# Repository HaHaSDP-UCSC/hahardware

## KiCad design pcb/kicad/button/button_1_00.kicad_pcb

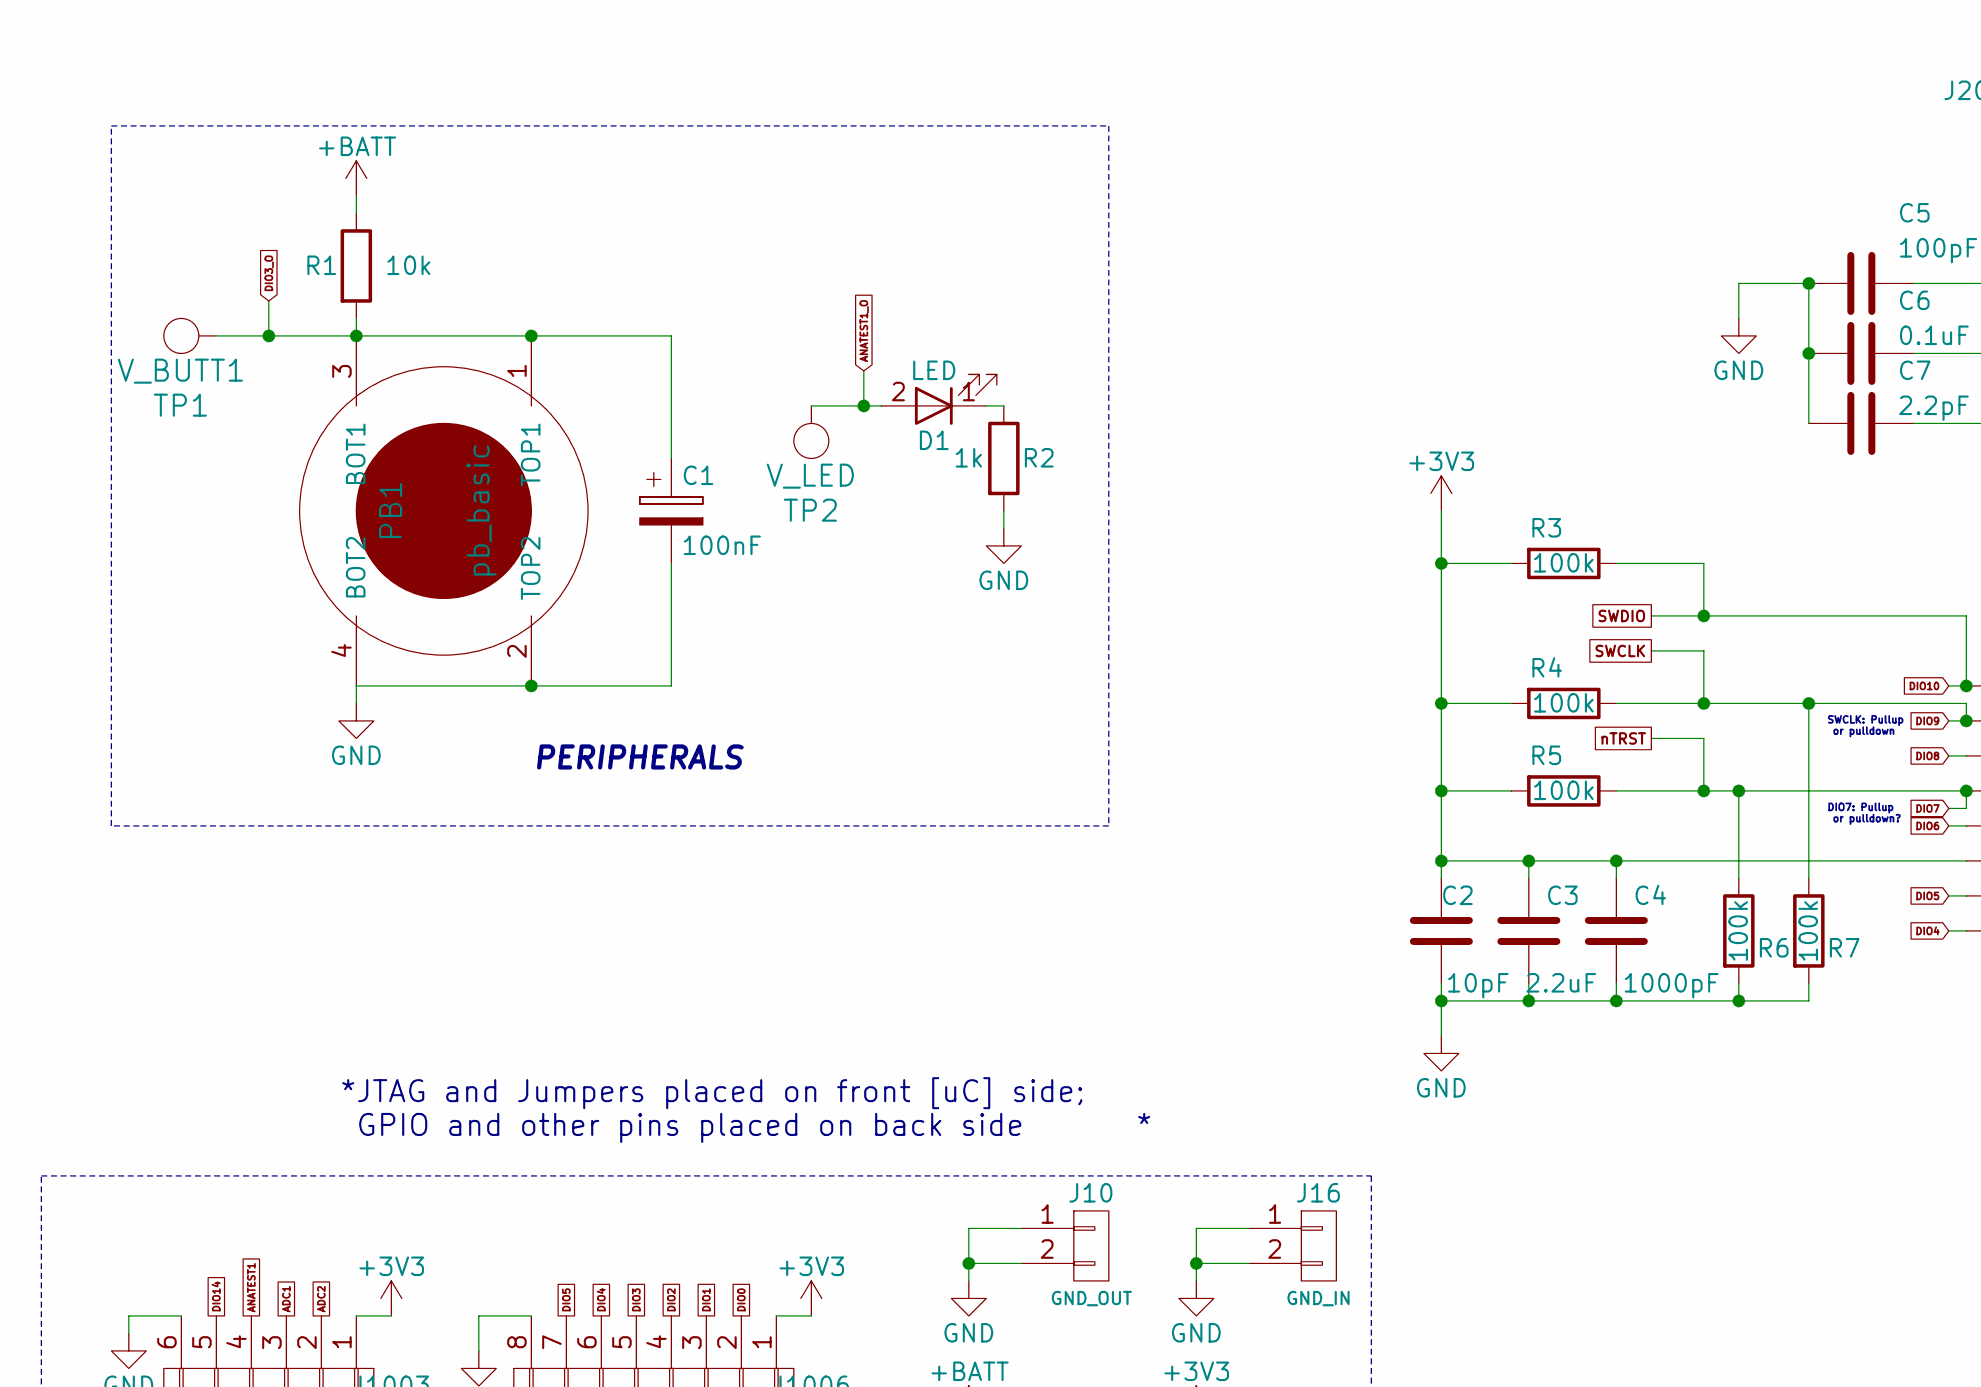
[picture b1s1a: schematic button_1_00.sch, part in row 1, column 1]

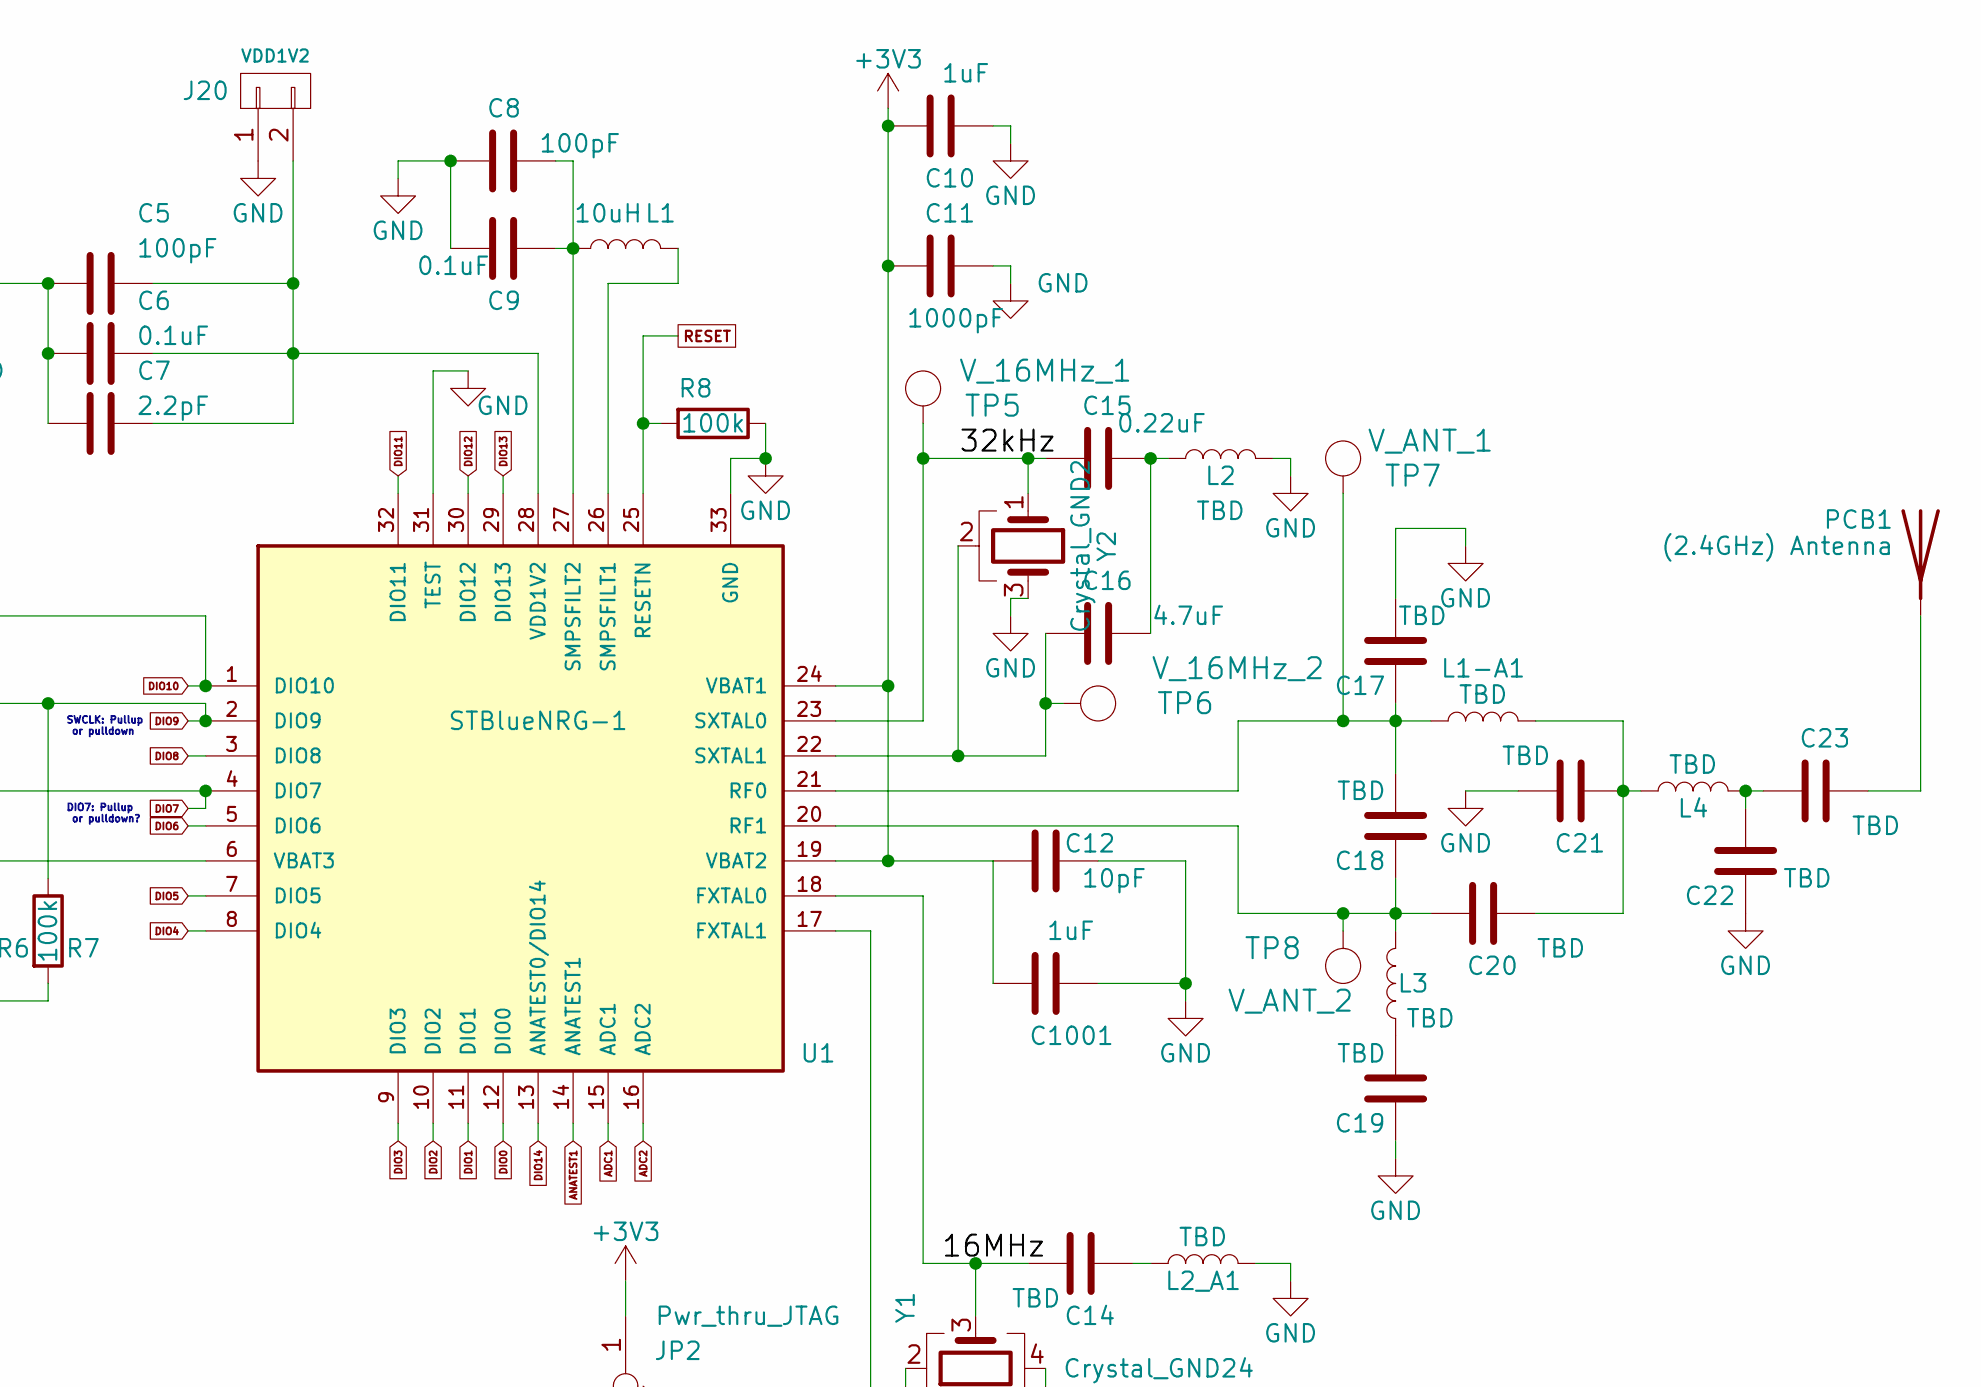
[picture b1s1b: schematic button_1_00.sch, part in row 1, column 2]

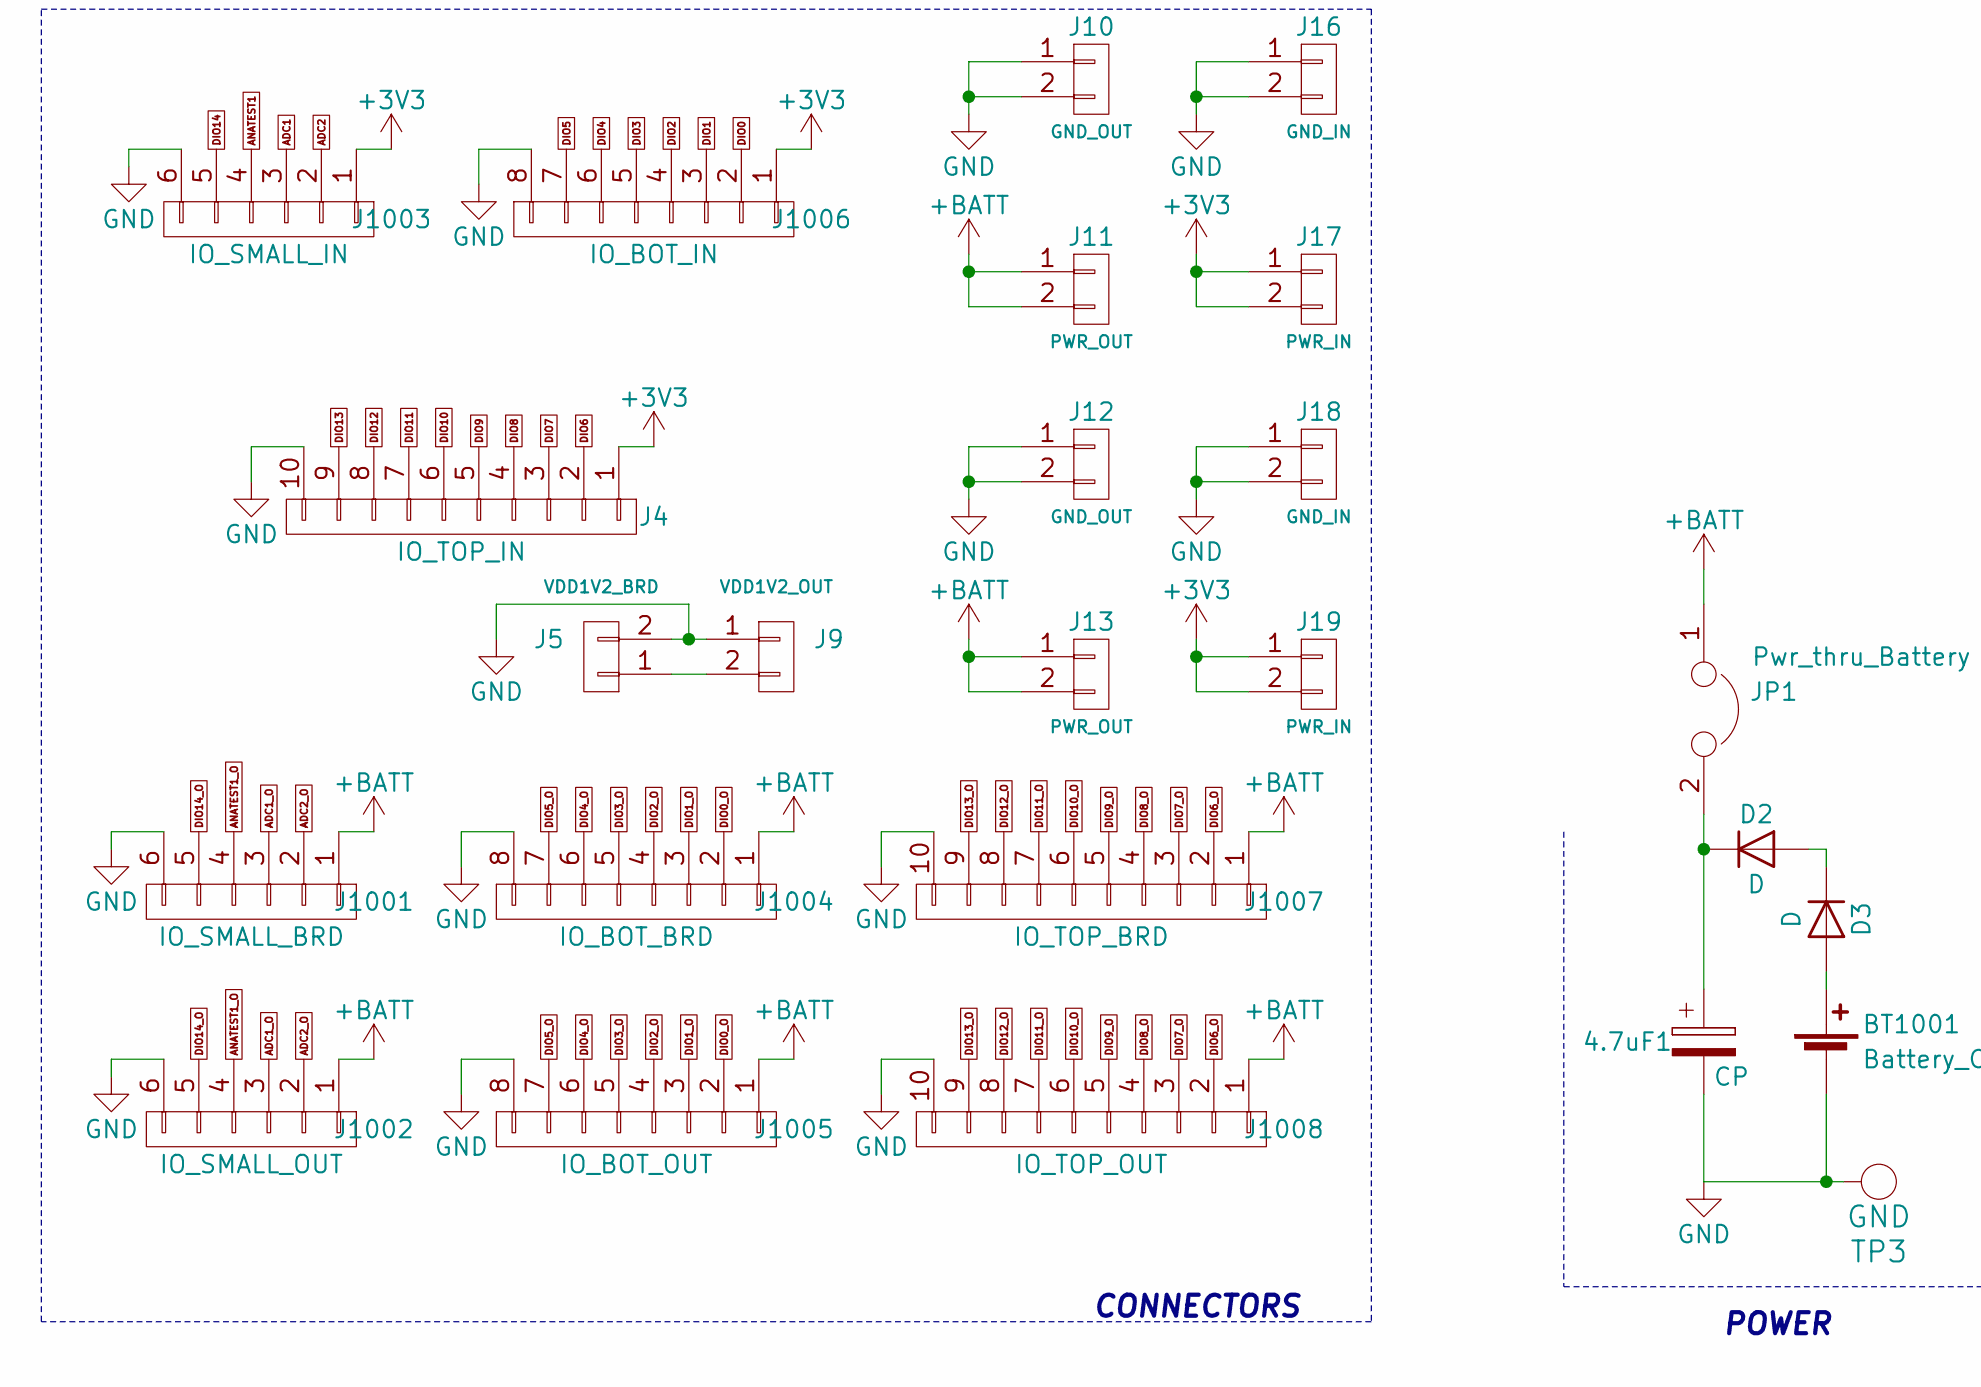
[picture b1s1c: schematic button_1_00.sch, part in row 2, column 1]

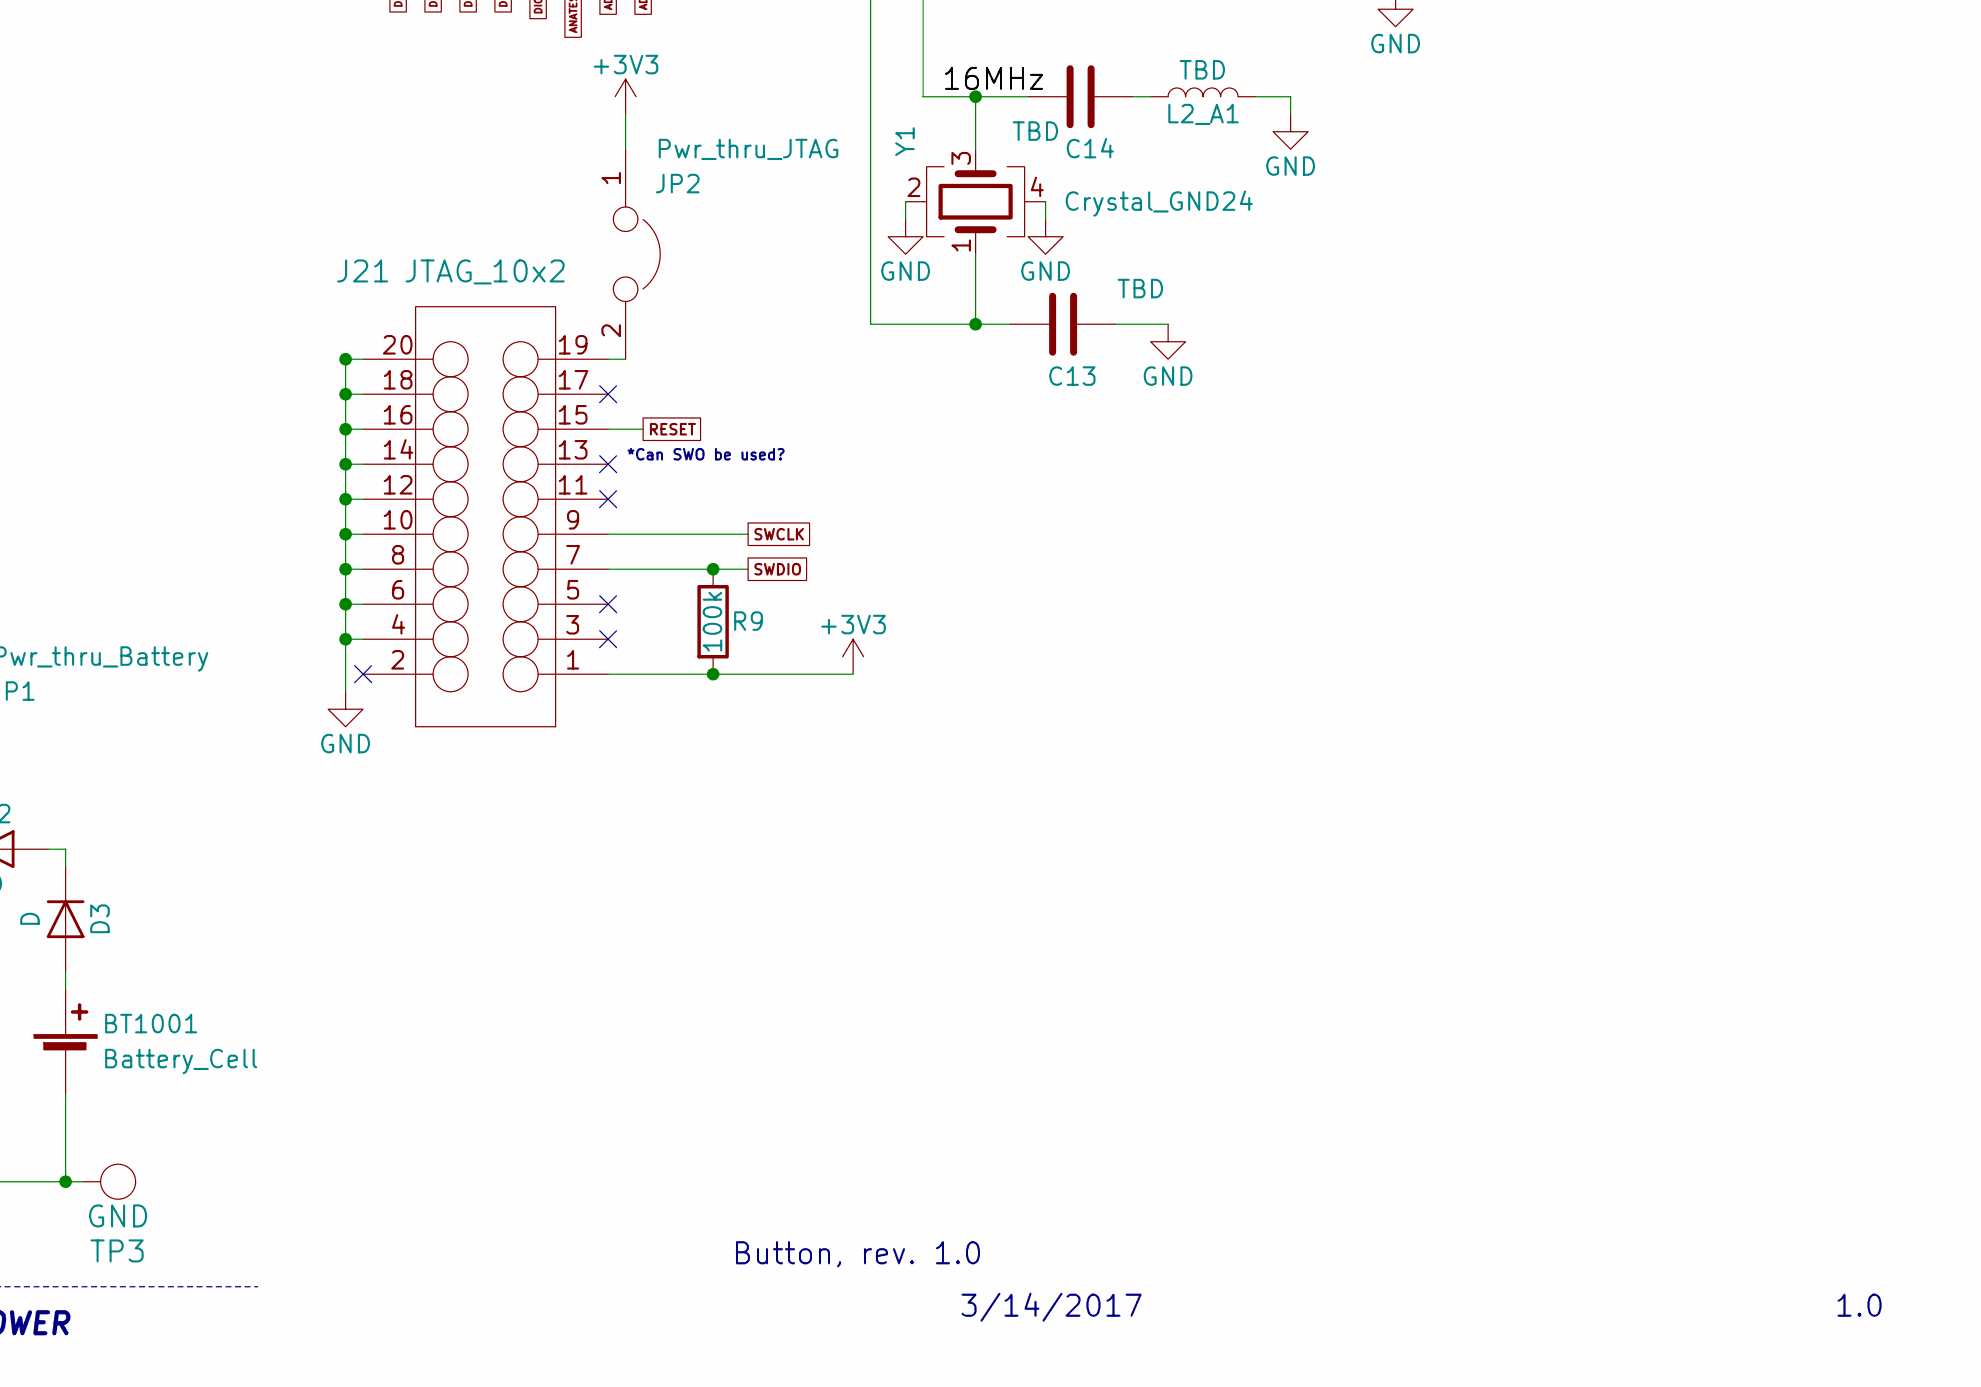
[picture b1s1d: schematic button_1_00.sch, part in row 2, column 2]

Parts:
4.7uF1: CP; C_0603
BT1001: Battery_Cell; Pin_Header_Straight_1x02_Pitch2.54mm
C1: 100nF; C_0603_HandSoldering
C2, C12: 10pF; C_0402
C3: 2.2uF; C_0402
C4, C11: 1000pF; C_0402
C5, C8: 100pF; C_0402
C6, C9: 0.1uF; C_0603
C7: 2.2pF; C_0402
C10, C1001: 1uF; C_0603
C13, C14, C17, C18, C19, C20, C21, C22, C23: TBD; C_0402
C15: 0.22uF; C_0402
C16: 4.7uF; C_0402
D1: LED; LED_0603
D2, D3: D; D_0603
J4: IO_TOP_IN; Pin_Header_Straight_1x10_Pitch2.54mm
J5: VDD1V2_BRD; Pin_Header_Straight_1x02_Pitch2.54mm
J9: VDD1V2_OUT; Pin_Header_Straight_1x02_Pitch2.54mm
J10, J12: GND_OUT; Pin_Header_Straight_1x02_Pitch2.54mm
J11, J13: PWR_OUT; Pin_Header_Straight_1x02_Pitch2.54mm
J16, J18: GND_IN; Pin_Header_Straight_1x02_Pitch2.54mm
J17, J19: PWR_IN; Pin_Header_Straight_1x02_Pitch2.54mm
J20: VDD1V2; Pin_Header_Straight_1x02_Pitch2.54mm
J21: JTAG_10x2; Multicomp_MC9A12-2034_2x10x2.54mm_Straight
J1001: IO_SMALL_BRD; Pin_Header_Straight_1x06_Pitch2.54mm
J1002: IO_SMALL_OUT; Pin_Header_Straight_1x06_Pitch2.54mm
J1003: IO_SMALL_IN; Pin_Header_Straight_1x06_Pitch2.54mm
J1004: IO_BOT_BRD; Pin_Header_Straight_1x08_Pitch2.54mm
J1005: IO_BOT_OUT; Pin_Header_Straight_1x08_Pitch2.54mm
J1006: IO_BOT_IN; Pin_Header_Straight_1x08_Pitch2.54mm
J1007: IO_TOP_BRD; Pin_Header_Straight_1x10_Pitch2.54mm
J1008: IO_TOP_OUT; Pin_Header_Straight_1x10_Pitch2.54mm
JP1: Pwr_thru_Battery; Pin_Header_Straight_1x02_Pitch2.54mm
JP2: Pwr_thru_JTAG; Pin_Header_Straight_1x02_Pitch2.54mm
L1: 10uH; Neosid_Inductor_SM-NE29_SMD1008
L1-A1, L2, L2_A1, L3, L4: TBD; Neosid_Inductor_SM0603CG
PB1: pb_basic
PCB1: (2.4GHz) Antenna; Molex_SMA_Jack_Edge_Mount
R1: 10k; R_0603
R2: 1k; R_0603
R3, R4, R5, R6, R7, R8: 100k; R_0603
R9: 100k; R_0805
TP1: V_BUTT1; TP_gen
TP2: V_LED; TP_gen
TP3: GND; TP_gen
TP5: V_16MHz_1; TP_gen
TP6: V_16MHz_2; TP_gen
TP7: V_ANT_1; TP_gen
TP8: V_ANT_2; TP_gen
U1: STBlueNRG-1; STBNRG1
Y1: Crystal_GND24; Crystal_SMD_2520-4pin_2.5x2.0mm
Y2: Crystal_GND2; Crystal_C26-LF_d2.1mm_l6.5mm_Horizontal_1EP_style1

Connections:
+3V3: C2.2, C3.2, C4.2, C10.2, C11.2, C12.2, C1001.2, J4.1, J17.1, J17.2, J19.1, J19.2, J21.1 (U_TG), J1003.1, J1006.1, JP2.1, R3.2, R4.2, R5.2, R9.2, U1.6 (VBAT3), U1.19 (VBAT2), U1.24 (VBAT1)
+BATT: J11.1, J11.2, J13.1, J13.2, J1001.1, J1002.1, J1004.1, J1005.1, J1007.1, J1008.1, JP1.1, R1.1
/16MHz: C14.2, U1.18 (FXTAL0), Y1.3
/32kHz: C15.2, TP5.1, U1.23 (SXTAL0), Y2.1
ADC1: J1003.3, U1.15 (ADC1)
ADC1_O: J1001.3, J1002.3
ADC2: J1003.2, U1.16 (ADC2)
ADC2_O: J1001.2, J1002.2
ANATEST1: J1003.4, U1.14 (ANATEST1)
ANATEST1_O: D1.2 (A), J1001.4, J1002.4, TP2.1
DIO0: J1006.2, U1.12 (DIO0)
DIO0_O: J1004.2, J1005.2
DIO1: J1006.3, U1.11 (DIO1)
DIO1_O: J1004.3, J1005.3
DIO2: J1006.4, U1.10 (DIO2)
DIO2_O: J1004.4, J1005.4
DIO3: J1006.5, U1.9 (DIO3)
DIO3_O: C1.1, J1004.5, J1005.5, PB1.1 (TOP1), PB1.3 (BOT1), R1.2, TP1.1
DIO4: J1006.6, U1.8 (DIO4)
DIO4_O: J1004.6, J1005.6
DIO5: J1006.7, U1.7 (DIO5)
DIO5_O: J1004.7, J1005.7
DIO6: J4.2, U1.5 (DIO6)
DIO6_O: J1007.2, J1008.2
DIO7: J4.3, R5.1, R6.1, U1.4 (DIO7)
DIO7_O: J1007.3, J1008.3
DIO8: J4.4, U1.3 (DIO8)
DIO8_O: J1007.4, J1008.4
DIO9: J4.5, J21.9 (TCK/SWCLK), R4.1, R7.1, U1.2 (DIO9)
DIO9_O: J1007.5, J1008.5
DIO10: J4.6, J21.7 (TMS/SWDIO), R3.1, R9.1, U1.1 (DIO10)
DIO10_O: J1007.6, J1008.6
DIO11: J4.7, U1.32 (DIO11)
DIO11_O: J1007.7, J1008.7
DIO12: J4.8, U1.30 (DIO12)
DIO12_O: J1007.8, J1008.8
DIO13: J4.9, U1.29 (DIO13)
DIO13_O: J1007.9, J1008.9
DIO14: J1003.5, U1.13 (ANATEST0/DIO14)
DIO14_O: J1001.5, J1002.5
GND: 4.7uF1.2, BT1001.2 (-), C1.2, C2.1, C3.1, C4.1, C5.2, C6.2, C7.2, C8.2, C9.2, C10.1, C11.1, C12.1, C13.1, C17.2, C19.1, C21.2, C22.1, C1001.1, J4.10, J5.2, J9.1, J10.1, J10.2, J12.1, J12.2, J16.1, J16.2, J18.1, J18.2, J20.1, J21.4 (GND), J21.6 (GND), J21.8 (GND), J21.10 (GND), J21.12 (GND), J21.14 (GND), J21.16 (GND), J21.18 (GND), J21.20 (GND), J1001.6, J1002.6, J1003.6, J1004.8, J1005.8, J1006.8, J1007.10, J1008.10, L2.2, L2_A1.2, PB1.2 (TOP2), PB1.4 (BOT2), R2.2, R6.2, R7.2, R8.1, TP3.1, U1.31 (TEST), U1.33 (GND), Y1.2, Y1.4, Y2.3
unnamed: 4.7uF1.1, D2.1 (K), JP1.2
unnamed: BT1001.1 (+), D3.2 (A)
unnamed: C5.1, C6.1, C7.1, J20.2, U1.28 (VDD1V2)
unnamed: C8.1, C9.1, L1.1, U1.27 (SMPSFILT2)
unnamed: C13.2, U1.17 (FXTAL1), Y1.1
unnamed: C14.1, L2_A1.1
unnamed: C15.1, C16.1, L2.1
unnamed: C16.2, TP6.1, U1.22 (SXTAL1), Y2.2
unnamed: C17.1, C18.2, L1-A1.1, TP7.1, U1.21 (RF0)
unnamed: C18.1, C20.2, L3.2, TP8.1, U1.20 (RF1)
unnamed: C19.2, L3.1
unnamed: C20.1, C21.1, L1-A1.2, L4.1
unnamed: C22.2, C23.2, L4.2
unnamed: C23.1, PCB1.1
unnamed: D1.1 (K), R2.1
unnamed: D2.2 (A), D3.1 (K)
unnamed: J5.1, J9.2
unnamed: J21.19 (U_TGPWR), JP2.2
unnamed: L1.2, U1.26 (SMPSFILT1)
RESET: J21.15 (nSRST), R8.2, U1.25 (RESETN)

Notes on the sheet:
Button, rev. 1.0
1.0
3/14/2017
POWER
CONNECTORS
PERIPHERALS
*JTAG and Jumpers placed on front [uC] side; GPIO and other pins placed on back side *
DIO7: Pullup or pulldown?
SWCLK: Pullup or pulldown
*Can SWO be used?

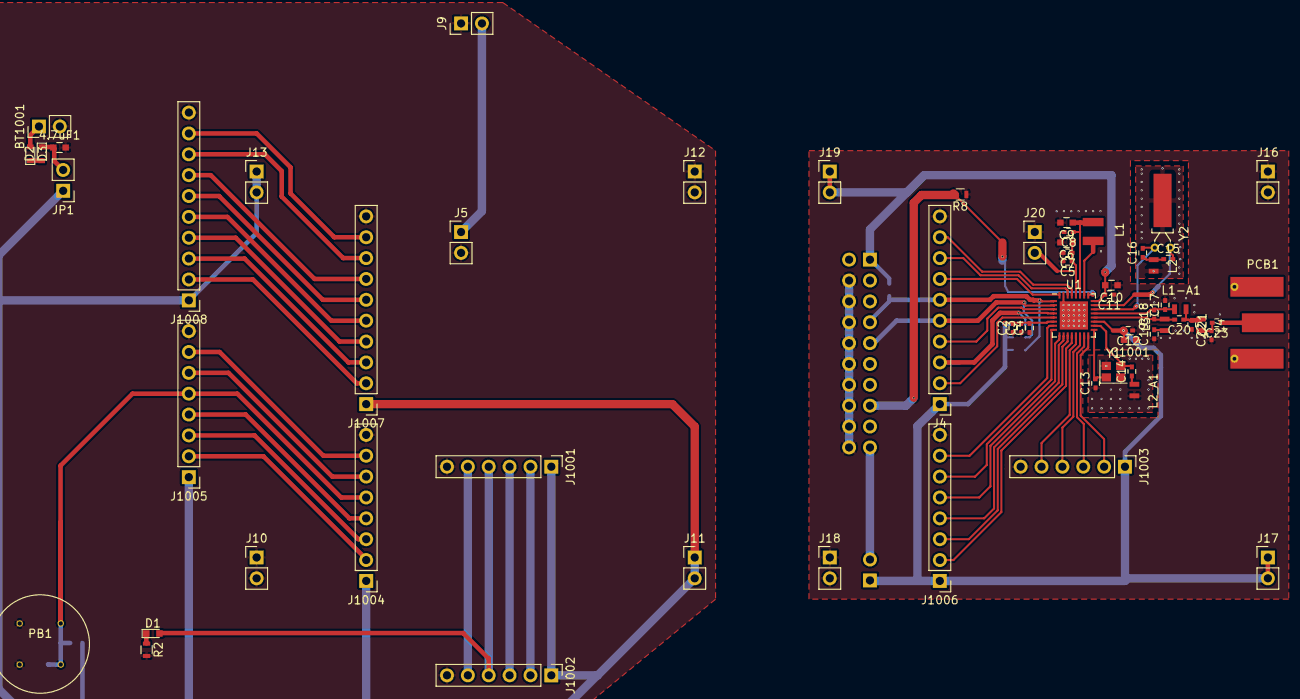
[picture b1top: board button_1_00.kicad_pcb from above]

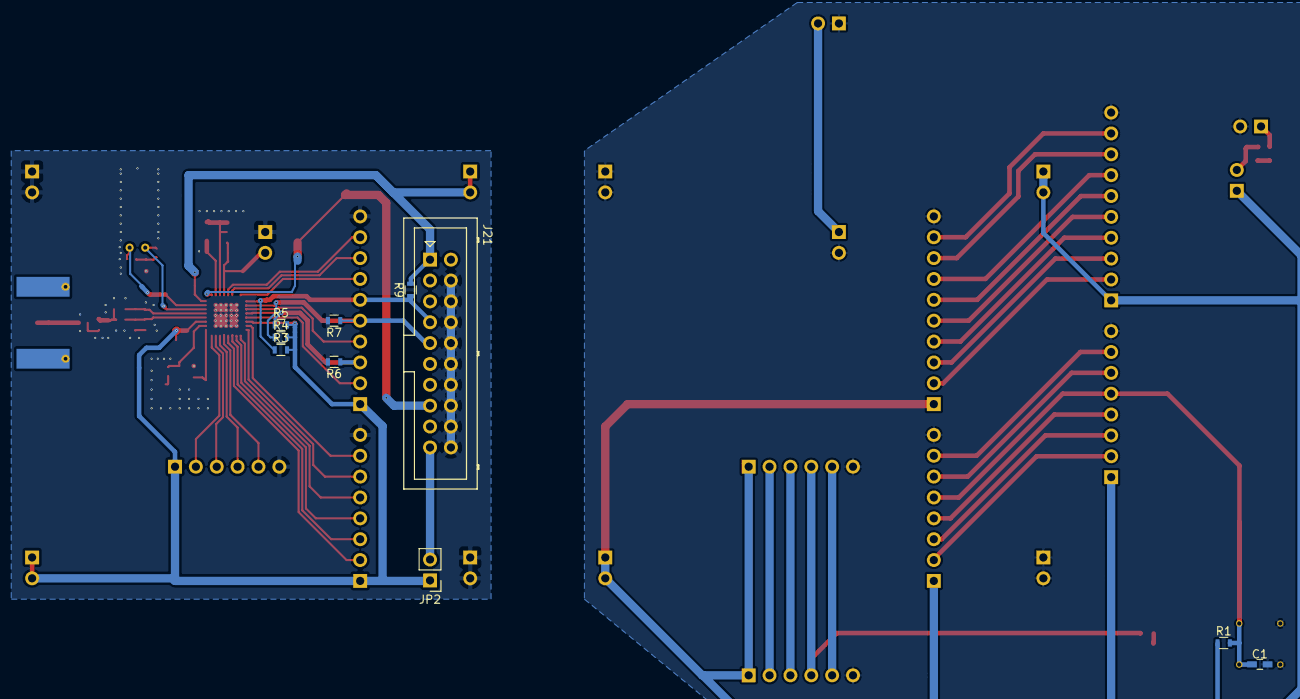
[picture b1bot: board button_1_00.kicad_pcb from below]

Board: 2 copper layers, 72 parts (10 on the bottom side), 61 nets.

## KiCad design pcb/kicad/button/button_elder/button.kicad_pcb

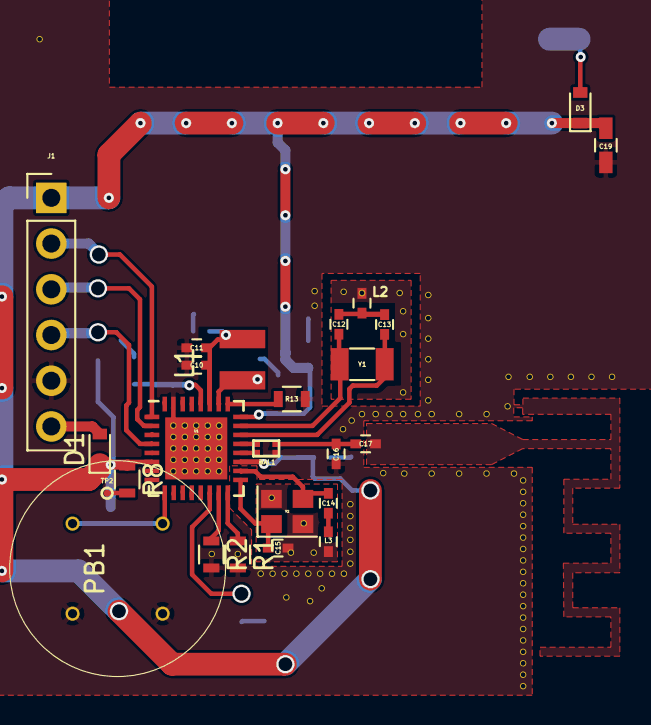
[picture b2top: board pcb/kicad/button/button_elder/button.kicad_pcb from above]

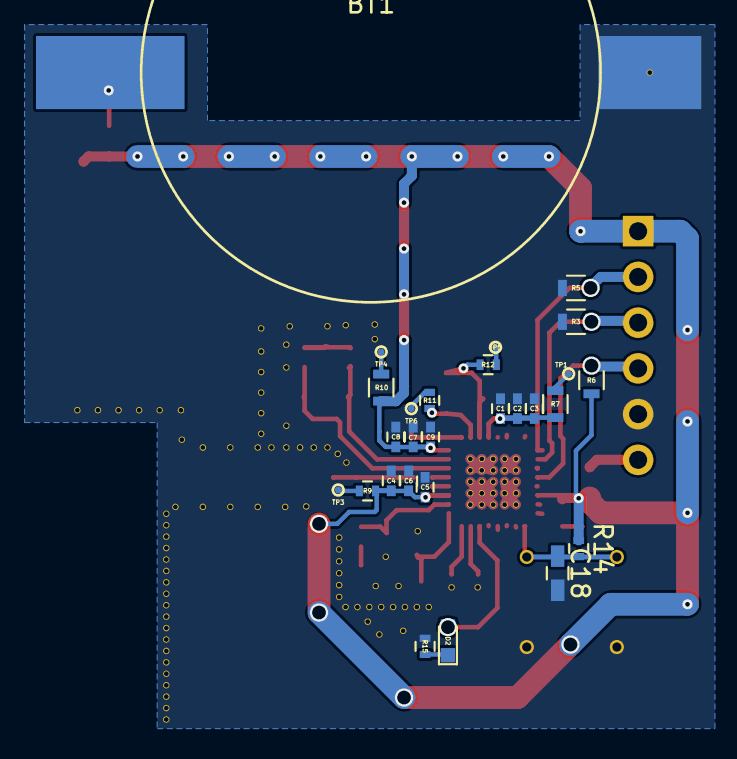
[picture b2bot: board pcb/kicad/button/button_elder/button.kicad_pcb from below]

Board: 2 copper layers, 52 parts (27 on the bottom side), 31 nets.

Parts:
BAL1: STBNR1_balun; BNRG1_balun
BT1: Battery_Cell; SMD_CoinCell
C1, C11: 100pF; C_0402
C2, C10: 0.1uF; C_0402
C3: 2.2pF; C_0402
C4, C9: 1000pF; C_0402
C5: 2.2uF; C_0402
C6, C7: 10pF; C_0402
C8: 1uF; C_0402
C12: 27pF; C_0402
C13, C14: 22pF; C_0402
C15: 18pF; C_0402
C16, C17: TBD; C_0402
C18: CP; C_0603_HandSoldering
C19: 1uF; C_0603_HandSoldering
D1: Power thru SWD; D_0603
D2: LED; LED_0603
D3: Power thru Battery; D_0603
J1: SWD with less; Pin_Header_Straight_1x06_Pitch2.54mm
L1: 10uH; Neosid_Inductor_SM-NE29_SMD1008
L2, L3: RFC; L_0402
PB1: pb_basic
R1, R2, R3, R5, R6, R13: 100k; R_0603
R7, R8, R10: 1k; R_0603
R9, R11, R12, R15: 1k; R_0402
R14: 10k; R_0402
TP1: VDD1V2; Measurement_Point_Round-SMD-tiniest
TP2, TP4: VBATT3; Measurement_Point_Round-SMD-tiniest
TP3: VBATT2; Measurement_Point_Round-SMD-tiniest
TP5: SMSPFILT2; Measurement_Point_Round-SMD-tiniest
TP6: SMPSFILT1; Measurement_Point_Round-SMD-tiniest
U1: STBlueNRG-1; STBNRG1
Y1: Xtal 32.768kHz; Crystal_SMD_3215-2pin_3.2x1.5mm
Y2: XTAL 16MHz; Crystal_SMD_2520-4pin_2.5x2.0mm

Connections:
+3V3: C4.2, C5.2, C6.2, C7.2, C8.2, C9.2, C19.1, D1.1, D3.1, J1.1, R6.2, R8.1, R9.1, R10.1, R14.1, U1.6, U1.19, U1.24
ADC1: R2.1, U1.15
ADC2: R1.1, U1.16
ANATEST1: D2.2, U1.14
DIO3: C18.1, PB1.1, PB1.3, R14.2, U1.9
DIO7: J1.4, R6.1, U1.4
DIO9: J1.3, R3.1, U1.2
DIO10: J1.2, R5.2, U1.1
GND: BAL1.4, BT1.2, C1.2, C2.2, C3.2, C4.1, C5.1, C6.1, C7.1, C8.1, C9.1, C10.2, C11.1, C15.1, C16.2, C17.1, C18.2, C19.2, J1.5, L2.2, L3.2, PB1.2, PB1.4, R1.2, R2.2, R3.2, R5.1, R13.2, R15.2, U1.31, U1.33, Y2.2, Y2.4
unnamed: BAL1.3, C16.1, C17.2
unnamed: BT1.1, D3.2
unnamed: C1.1, C2.1, C3.1, R7.1, U1.28
unnamed: C10.1, C11.2, L1.2, R12.2, U1.27
unnamed: C12.1, C13.1, L2.1
unnamed: C12.2, U1.23, Y1.1
unnamed: C13.2, U1.22, Y1.2
unnamed: C14.1, L3.1
unnamed: C14.2, U1.18, Y2.3
unnamed: C15.2, U1.17, Y2.1
unnamed: D1.2, J1.6
unnamed: D2.1, R15.1
unnamed: L1.1, R11.1, U1.26
unnamed: R7.2, TP1.1
unnamed: R8.2, TP2.1
unnamed: R9.2, TP3.1
unnamed: R10.2, TP4.1
unnamed: R11.2, TP6.1
unnamed: R12.1, TP5.1
RESET: R13.1, U1.25
RF0: BAL1.1, U1.21
RF1: BAL1.2, U1.20

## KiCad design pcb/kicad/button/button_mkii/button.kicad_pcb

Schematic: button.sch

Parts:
C1, C22: 1uF; C_0805
C2, C23: 0.1uF; C_0603
C3, C24: 0.01uF; C_0402
C4, C7: 0.01uF; C_0805
C5, C8: 1000pF; C_0603
C6, C9: 10pF; C_0402
C10: 0.1uF; C_0402
C11: 100pF; C_0402
C12, C14: 27pF; C_0402
C13: 22pF; C_0402
C15: 33pF; C_0402
C20, C21: 1uF; C_0402
J1: SWD; Pin_Header_Straight_1x08_Pitch2.54mm
J2: RESET_CONN; Pin_Header_Straight_1x02_Pitch2.54mm
J3: ADC_OUT; Pin_Header_Straight_1x03_Pitch2.54mm
L1: 10uH; Neosid_Inductor_SM-NE29_SMD1008
R3, R4, R5, R13: 100k; R_0402
R6, R9, R11, R12, R16: 1k; R_0402
R7, R8, R10: 1k; R_0603
TP1: VDD1V2; Measurement_Point_Round-SMD-tiniest
TP2, TP4: VBATT3; Measurement_Point_Round-SMD-tiniest
TP3: VBATT2; Measurement_Point_Round-SMD-tiniest
TP5: SMSPFILT2; Measurement_Point_Round-SMD-tiniest
TP6: SMPSFILT1; Measurement_Point_Round-SMD-tiniest
TP7: Xtal32MHz; Measurement_Point_Round-SMD-tiniest
TP8: Xtal32kHz; Measurement_Point_Round-SMD-tiniest
U1: STBlueNRG-1; STBNRG1
U2: TLV1117LV-3V; SOT-223
Y1: Xtal 32.768kHz; Crystal_SMD_3215-2pin_3.2x1.5mm
Y2: XTAL 32MHz; Crystal_SMD_2520-4pin_2.5x2.0mm

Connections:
/DIO2_LED: U1.10 (DIO2); also elsewhere on the board
/DIO12_BUTTON: U1.30 (DIO12); also elsewhere on the board
/RF0: U1.21 (RF0); also elsewhere on the board
/RF1: U1.20 (RF1); also elsewhere on the board
ADC1: J3.2, U1.15 (ADC1)
ADC2: J3.3, U1.16 (ADC2)
DIO7: J1.4, R4.2, U1.4 (DIO7)
DIO9: J1.5, R3.1, U1.2 (DIO9)
DIO10: J1.6, R5.2, U1.1 (DIO10)
GND: C1.2, C2.2, C3.2, C4.2, C5.2, C6.2, C7.1, C8.1, C9.1, C10.2, C11.1, C12.1, C13.1, C14.1, C15.1, C20.1, C21.1, C22.1, C23.1, C24.1, J1.7, J2.2, J3.1, R3.2, R5.1, R13.1, U1.31 (TEST), U1.33 (GND), U2.1 (GND), Y2.2, Y2.4; also elsewhere on the board
unnamed: C1.1, C2.1, C3.1, R7.2, U1.28 (VDD1V2)
unnamed: C10.1, C11.2, L1.2, R12.2, U1.27 (SMPSFILT2)
unnamed: C12.2, R16.1, U1.23 (SXTAL0), Y1.1
unnamed: C13.2, U1.22 (SXTAL1), Y1.2
unnamed: C14.2, R6.1, U1.18 (FXTAL0), Y2.3
unnamed: C15.2, U1.17 (FXTAL1), Y2.1
unnamed: C20.2, J1.1, U2.3 (VIN)
unnamed: J1.2, U1.12 (DIO0)
unnamed: J1.3, U1.11 (DIO1)
unnamed: J2.1, R13.2, U1.25 (RESETN)
unnamed: L1.1, R11.1, U1.26 (SMPSFILT1)
unnamed: R6.2, TP7.1
unnamed: R7.1, TP1.1
unnamed: R8.1, TP2.1
unnamed: R9.2, TP3.1
unnamed: R10.2, TP4.1
unnamed: R11.2, TP6.1
unnamed: R12.1, TP5.1
unnamed: R16.2, TP8.1

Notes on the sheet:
Button, rev 2.0
1.0
5/21/2017
32.768kHz Oscillator
*NOTE: Resistors for testing different boot configs. -> Omit until needed. *

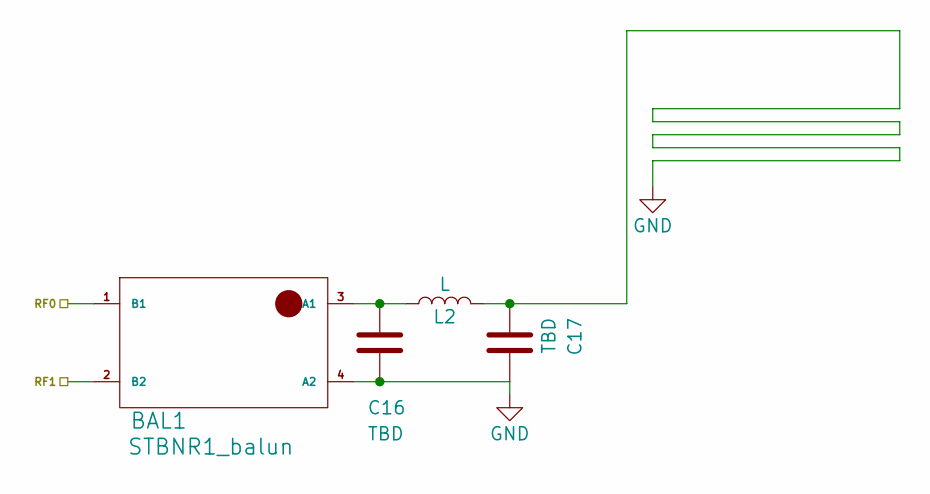
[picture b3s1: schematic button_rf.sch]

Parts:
BAL1: STBNR1_balun; BNRG1_balun
C16, C17: TBD; C_0402
L2: L; C_0603_HandSoldering

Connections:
/RF0: BAL1.1 (B1); also elsewhere on the board
/RF1: BAL1.2 (B2); also elsewhere on the board
GND: BAL1.4 (A2), C16.2, C17.1, C17.2, L2.2; also elsewhere on the board
unnamed: BAL1.3 (A1), C16.1, L2.1

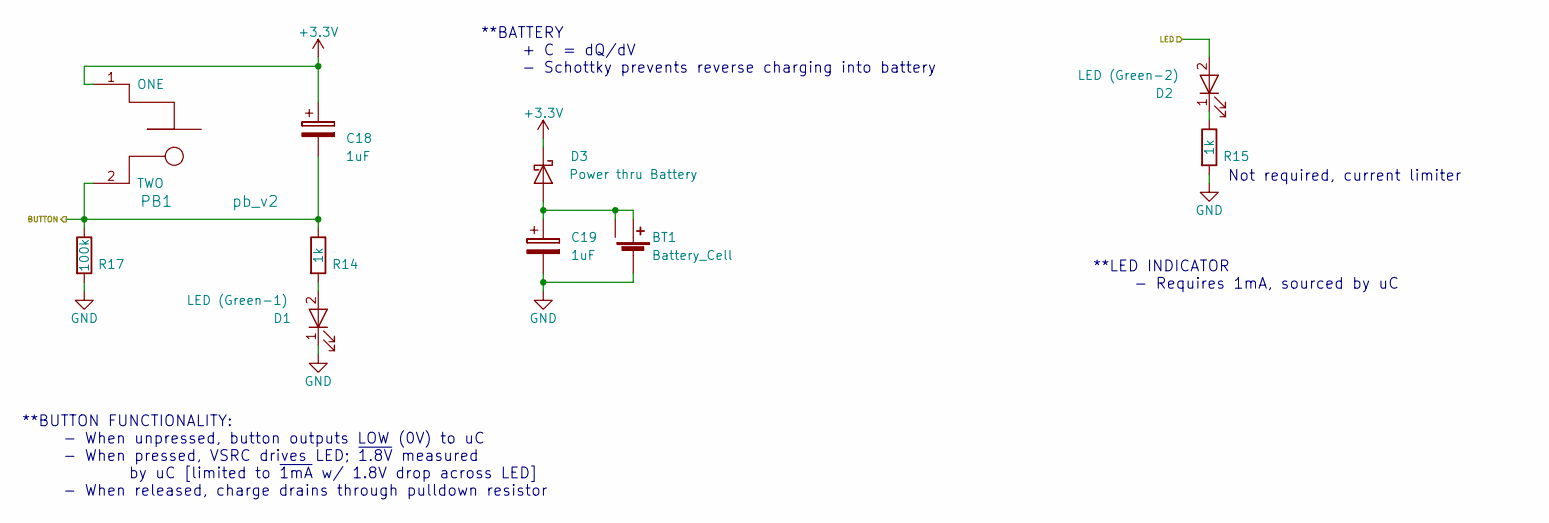
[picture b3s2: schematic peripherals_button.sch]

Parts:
BT1: Battery_Cell; CoinCell_holder_1060x630
C18, C19: 1uF; C_0603_HandSoldering
D1: LED (Green-1); LED_0402
D2: LED (Green-2); LED_0402
D3: Power thru Battery; D_0603
PB1: pb_v2; SW_PUSH-12mm
R14, R15: 1k; R_0402
R17: 100k; R_0402

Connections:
/DIO2_LED: D2.2 (A); also elsewhere on the board
/DIO12_BUTTON: C18.2, PB1.2 (TWO), R14.1, R17.1; also elsewhere on the board
GND: BT1.3 (-), C19.2, D1.1 (K), R15.2, R17.2; also elsewhere on the board
unnamed: BT1.1 (+), BT1.2 (++), C19.1, D3.2 (A)
unnamed: D1.2 (A), R14.2
unnamed: D2.1 (K), R15.1

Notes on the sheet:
**BUTTON FUNCTIONALITY: - When unpressed, button outputs LOW (0V) to uC - When pressed, VSRC drives LED; ~1.8V measured by uC [limited to ~1mA w/ 1.8V drop across LED] - When released, charge drains through pulldown resistor
**BATTERY + C = dQ/dV - Schottky prevents reverse charging into battery
**LED INDICATOR - Requires 1mA, sourced by uC
Not required, current limiter

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
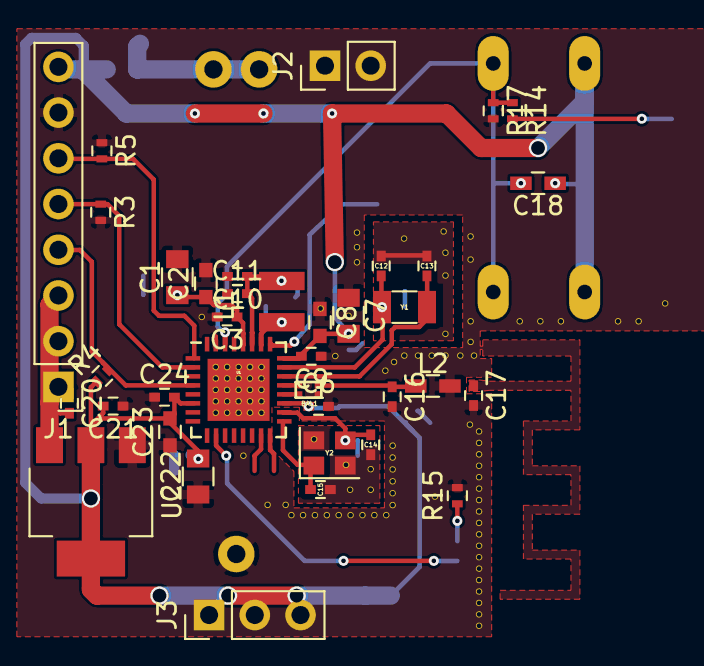
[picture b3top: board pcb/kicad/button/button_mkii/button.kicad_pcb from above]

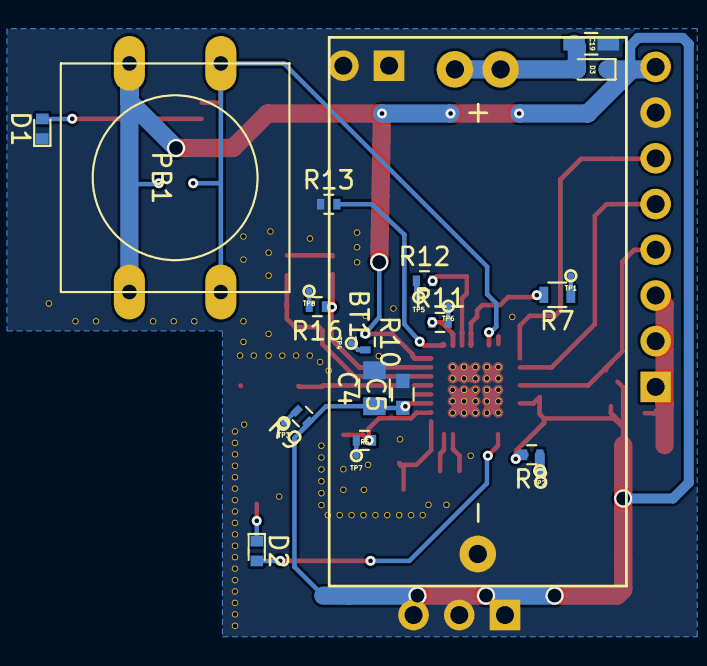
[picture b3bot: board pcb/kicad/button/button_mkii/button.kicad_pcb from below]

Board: 2 copper layers, 62 parts (25 on the bottom side), 34 nets.
